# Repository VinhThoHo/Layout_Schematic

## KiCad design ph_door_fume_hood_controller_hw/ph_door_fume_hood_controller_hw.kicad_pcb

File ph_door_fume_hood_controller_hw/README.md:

# ph_door_fume_hood_controller_hw
This is hardware sample and reactor controller for project the door fume hood.

# Description

## Features:
    * Power input 24VDC (isolation 24VDC - 5VDC 1W)
    * 3 sensor input are activated at level low.
    * 4 output are activated at level low.
    * 4 input are activated at level high.
    * Control step mottor with current upto 4A.
    * Communication 485 (status, control signal,...), I2C, analog signal.
# Hardware
## Schematics

[Download](./ph_door_fume_hood_controller_hw.pdf)

## PCB Layout

## 3D Review

## Pinout

# Gerber

[Download](./gerber/gerber_ph_door_fume_hood_controller_hw.zip)

# BOMLIST

[Download](./assets/ph_door_fume_hood_controller_hw.csv)

# License

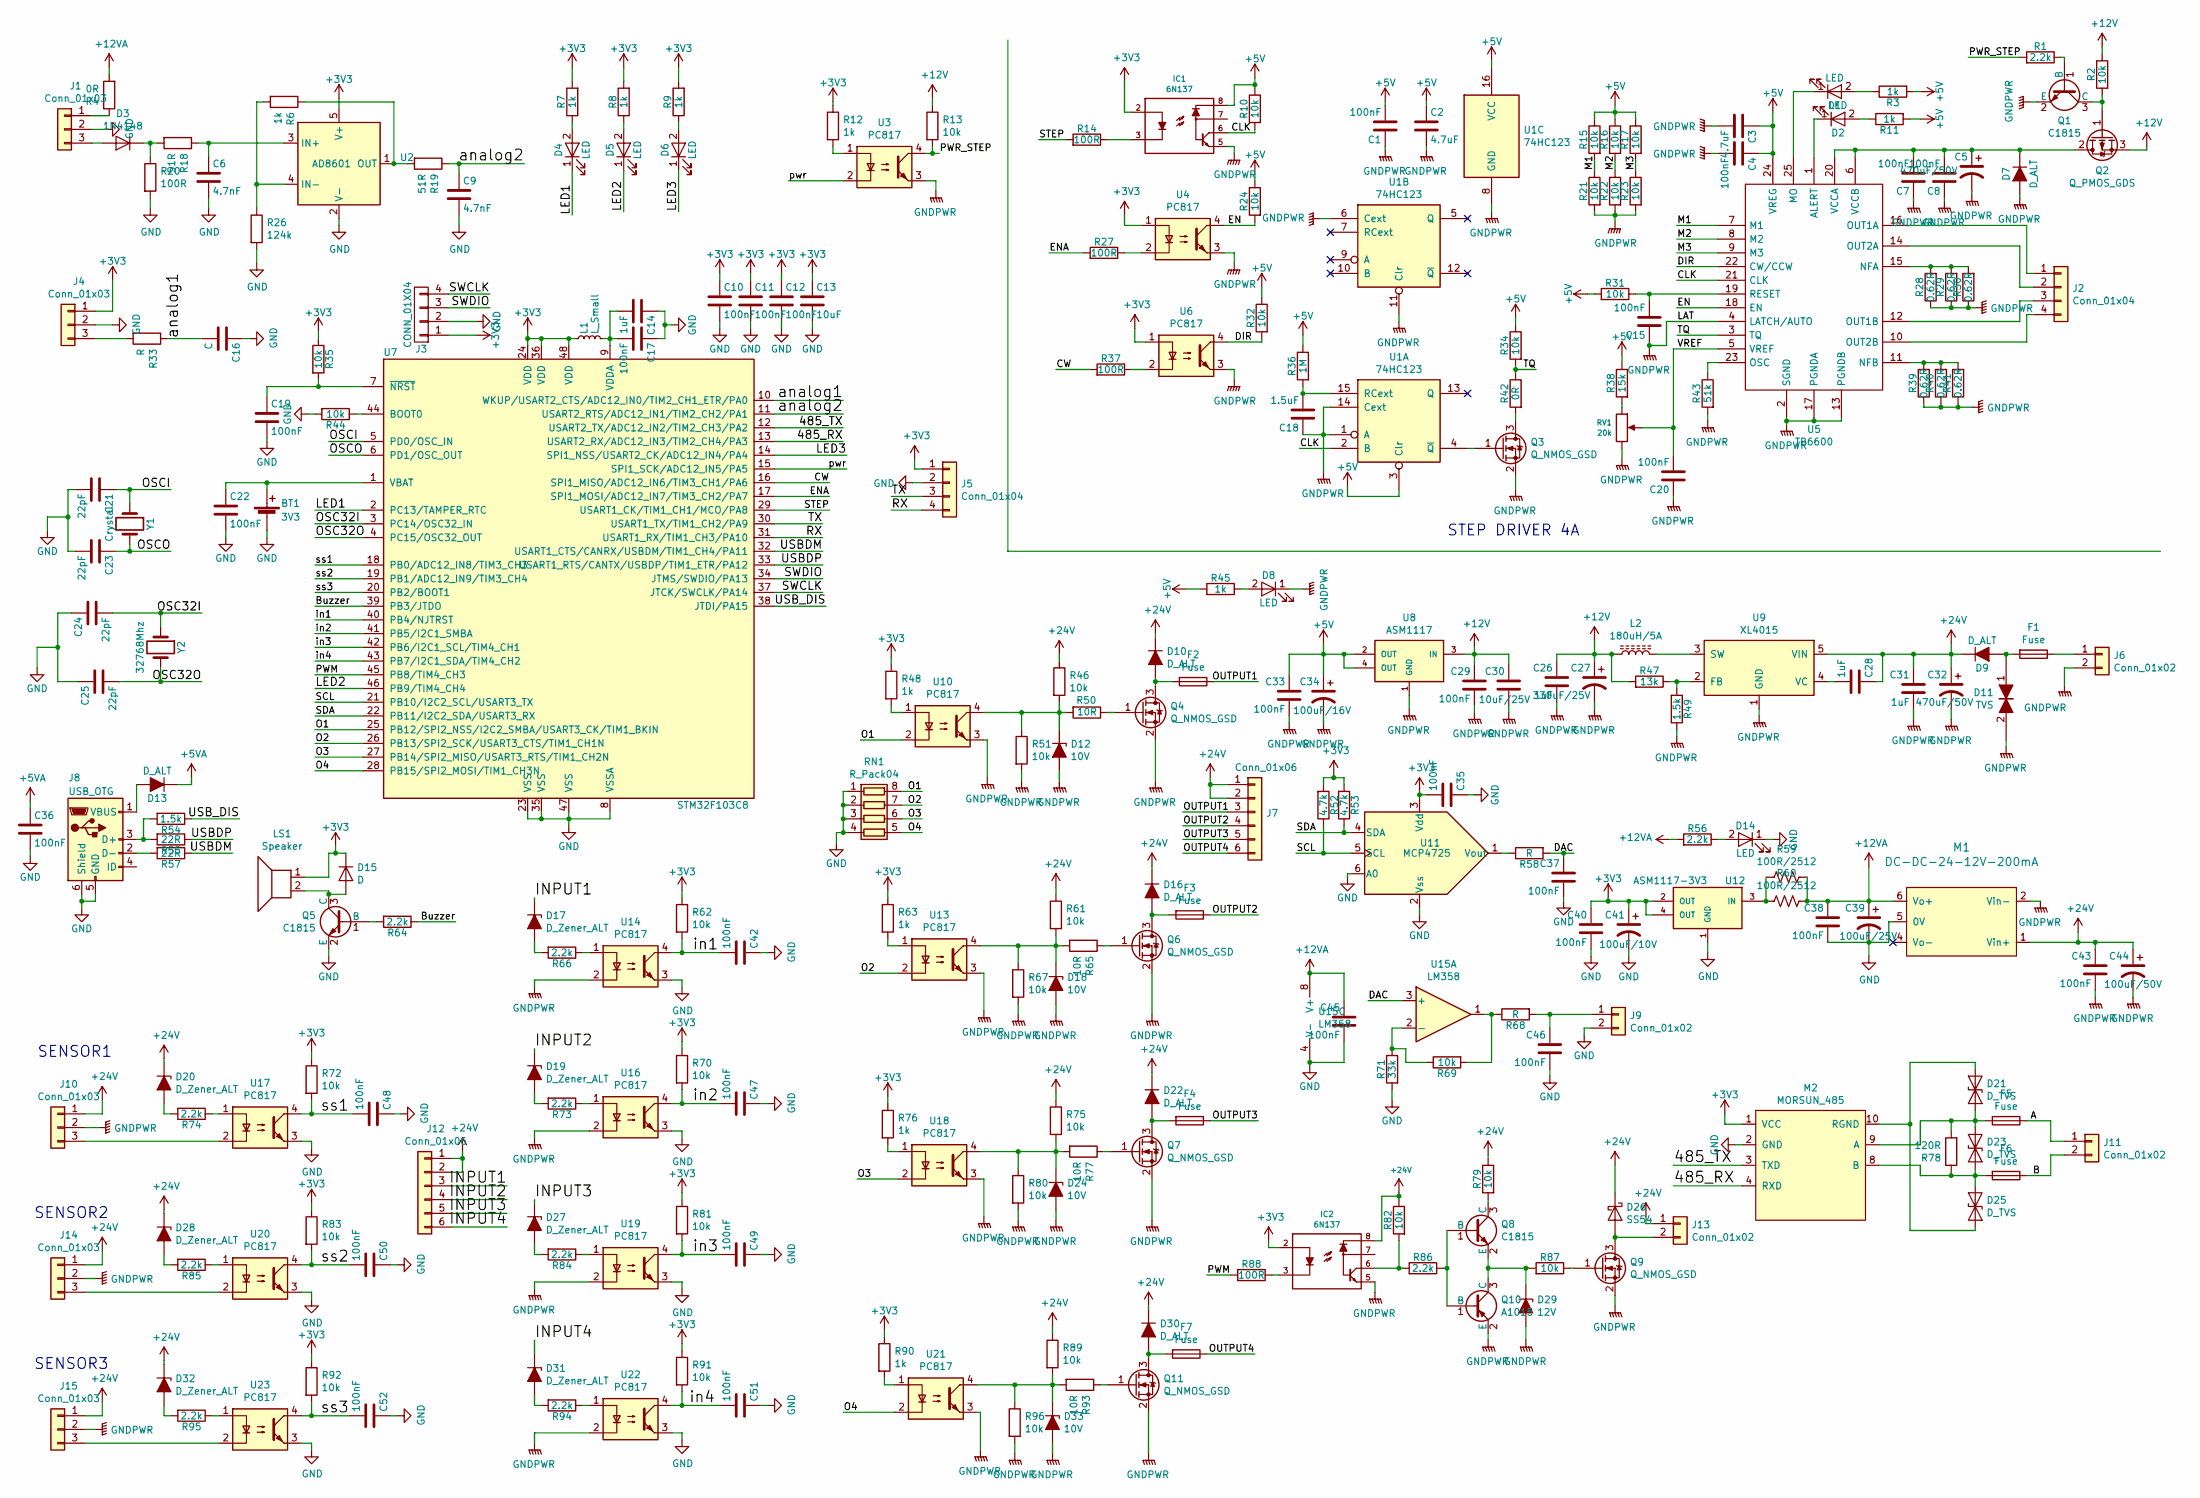
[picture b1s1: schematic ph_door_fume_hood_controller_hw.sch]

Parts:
BT1: 3V3; BT3V3
C1, C4, C7, C8, C10, C11, C12, C15, C17, C19, C20, C22, C29, C33, C35, C36, C37, C38, C40, C42, C43, C45, C46, C47, C48, C49, C50, C51, C52: 100nF; C_0805_2012Metric_Pad1.15x1.40mm_HandSolder
C2, C3: 4.7uF; C_1206_3216Metric_Pad1.42x1.75mm_HandSolder
C5: 470uF/50V; C_1210_3225Metric_Pad1.42x2.65mm_HandSolder
C6, C9: 4.7nF; C_0805_2012Metric_Pad1.15x1.40mm_HandSolder
C13: 10uF; C_1206_3216Metric_Pad1.42x1.75mm_HandSolder
C14, C26, C28, C31: 1uF; C_0805_2012Metric_Pad1.15x1.40mm_HandSolder
C16: C; C_0805_2012Metric_Pad1.15x1.40mm_HandSolder
C18: 1.5uF; C_0805_2012Metric_Pad1.15x1.40mm_HandSolder
C21, C23, C24, C25: 22pF; C_0805_2012Metric_Pad1.15x1.40mm_HandSolder
C27: 330uF/25V; CP_Elec_8x10.5
C30: 10uF/25V; C_1210_3225Metric_Pad1.42x2.65mm_HandSolder
C32: 470uF/50V; CP_Elec_10x14.3
C34: 100uF/16V; CP_Elec_6.3x5.4
C39: 100uF/25V; CP_EIA-7343-20_Kemet-V_Pad2.25x2.55mm_HandSolder
C41: 100uF/10V; CP_EIA-3528-15_AVX-H_Pad1.50x2.35mm_HandSolder
C44: 100uF/50V; CP_EIA-7343-31_Kemet-D_Pad2.25x2.55mm_HandSolder
D1, D2, D4, D5, D6, D8, D14: LED; LED_0805_2012Metric_Pad1.15x1.40mm_HandSolder
D3: 1N4148; D_SOD-323_HandSoldering
D7, D9, D10, D16, D22, D30: D_ALT; D_SMA_Standard
D11: TVS; D_SMA_Standard
D12, D18, D24, D33: 10V; SOD-80
D13: D_ALT; D_SOD-323F
D15: D; D_SOD-323F
D17, D19, D20, D27, D28, D31, D32: D_Zener_ALT; SOD-80
D21, D23, D25: D_TVS; D_SMA_Standard
D26: SS54; D_SMA_Standard
D29: 12V; SOD-80
F1: Fuse; Fuseholder5x20_horiz_SemiClosed_Casing10x25mm
F2, F3, F4, F5, F6, F7: Fuse; Fuse_SMD1812
IC1: 6N137; Diodes_PSOP-8
IC2: 6N137; SMDIP-8_W9.53mm
J1, J4: Conn_01x03; PinSocket_1x03_P2.54mm_Vertical
J2: Conn_01x04; TerminalBlock_WAGO-236_2Stift_R5mm_4pol
J3: CONN_01X04; PinHeader_1x04_P2.54mm_Vertical
J5: Conn_01x04; PinHeader_1x04_P2.54mm_Vertical
J6: Conn_01x02; TerminalBlock_WAGO-236_2Stift_R5mm_2pol
J7, J12: Conn_01x06; TerminalBlock_WAGO_2.54mm_6P
J8: USB_OTG; USB_Micro-B
J9: Conn_01x02; PinSocket_1x02_P2.54mm_Vertical
J10, J14, J15: Conn_01x03; TerminalBlock_WAGO_2.54mm_3P
J11, J13: Conn_01x02; TerminalBlock_WAGO_2.54mm_2P
L1: L_Small; L_0805_2012Metric_Pad1.15x1.40mm_HandSolder
L2: 180uH/5A; Inductor_5A
LS1: Speaker; Buzzer_15x7.5RM7.6
M1: DC-DC-24-12V-200mA; MORNSUN-A2412S-2W
M2: MORSUN_485
Q1, Q5, Q8: C1815; SOT-23
Q2: Q_PMOS_GDS; TO-252-2
Q3, Q4, Q6, Q7, Q9, Q11: Q_NMOS_GSD; SOT-23
Q10: A1015; SOT-23
R1, R56, R64, R66, R73, R74, R84, R85, R86, R94, R95: 2.2k; R_0805_2012Metric_Pad1.15x1.40mm_HandSolder
R2, R10, R13, R15, R16, R17, R21, R22, R23, R24, R31, R32, R34, R35, R44, R46, R51, R61, R62, R67, R69, R70, R72, R75, R79, R80, R81, R82, R83, R87, R89, R91, R92, R96: 10k; R_0805_2012Metric_Pad1.15x1.40mm_HandSolder
R3, R6, R7, R8, R9, R11, R12, R45, R48, R63, R76, R90: 1k; R_0805_2012Metric_Pad1.15x1.40mm_HandSolder
R4, R42: 0R; R_0805_2012Metric_Pad1.15x1.40mm_HandSolder
R14, R20, R27, R37, R88: 100R; R_0805_2012Metric_Pad1.15x1.40mm_HandSolder
R18, R19: 51R; R_0805_2012Metric_Pad1.15x1.40mm_HandSolder
R26: 124k; R_0805_2012Metric_Pad1.15x1.40mm_HandSolder
R28, R29, R30, R39, R40, R41: 0.62R; R_2512_6332Metric_Pad1.52x3.35mm_HandSolder
R33, R58, R68: R; R_0805_2012Metric_Pad1.15x1.40mm_HandSolder
R36: 1M; R_0805_2012Metric_Pad1.15x1.40mm_HandSolder
R38: 15k; R_0805_2012Metric_Pad1.15x1.40mm_HandSolder
R43: 51k; R_0805_2012Metric_Pad1.15x1.40mm_HandSolder
R47: 13k; R_0805_2012Metric_Pad1.15x1.40mm_HandSolder
R49, R54: 1.5k; R_0805_2012Metric_Pad1.15x1.40mm_HandSolder
R50, R65, R77, R93: 10R; R_0805_2012Metric_Pad1.15x1.40mm_HandSolder
R52, R53: 4.7k; R_0805_2012Metric_Pad1.15x1.40mm_HandSolder
R55, R57: 22R; R_0805_2012Metric_Pad1.15x1.40mm_HandSolder
R59, R60: 100R/2512; R_2512_6332Metric_Pad1.52x3.35mm_HandSolder
R71: 33k; R_0805_2012Metric_Pad1.15x1.40mm_HandSolder
R78: 120R; R_0805_2012Metric_Pad1.15x1.40mm_HandSolder
RN1: R_Pack04; R_Array_Convex_4x0603
RV1: 20k; VR-3362P
U1: 74HC123; SOIC-16W_5.3x10.2mm_Pitch1.27mm
U2: AD8601; SOT-23-5
U3, U4, U6, U10, U13, U14, U16, U17, U18, U19, U20, U21, U22, U23: PC817; Optocoupler_SMD
U5: TB6600
U7: STM32F103C8; LQFP-48_7x7mm_Pitch0.5mm
U8: ASM1117; SOT-223
U9: XL4015; TO-263-5_TabPin3
U11: MCP4725; SOT-23-6_Handsoldering
U12: ASM1117-3V3; SOT-223
U15: LM358; SOP-8_3.76x4.96mm_P1.27mm
Y1: Crystal; Crystal_SMD_HC49-SD
Y2: 32768Mhz; Crystal_Round_Horizontal_3mm_smd

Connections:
+3V3: C10.1, C11.1, C12.1, C13.1, C35.2, C40.1, C41.1, D15.1 (K), IC1.2, IC2.2, J3.1, J4.1, J5.1, L1.1, LS1.1, M2.1 (VCC), R7.2, R8.2, R9.2, R12.1, R35.1, R48.1, R52.2, R53.2, R62.1, R63.1, R70.1, R72.1, R76.1, R81.1, R83.1, R90.1, R91.1, R92.1, U2.5 (V+), U4.1, U6.1, U7.24 (VDD), U7.36 (VDD), U7.48 (VDD), U11.3 (Vdd), U12.2 (OUT), U12.4 (OUT)
+5V: C1.2, C2.1, C3.1, C4.1, C33.1, C34.1, IC1.8, R3.2, R10.1, R11.2, R15.1, R16.1, R17.1, R24.1, R31.2, R32.1, R34.1, R36.1, R38.1, R45.2, U1.3 (Clr), U1.16 (VCC), U5.24 (VREG), U8.2 (OUT), U8.4 (OUT)
+5VA: C36.1, D13.1 (K)
+12V: C26.1, C27.1, C29.1, C30.1, L2.1, Q2.3 (S), R2.1, R13.1, R47.2, U8.3 (IN)
+12VA: C38.1, C39.1, C45.1, M1.6 (Vo+), R4.2, R56.2, R59.1, R60.1, U15.8 (V+)
/485_RX: M2.4 (RXD), U7.13 (USART2_RX/ADC12_IN3/TIM2_CH4/PA3)
/485_TX: M2.3 (TXD), U7.12 (USART2_TX/ADC12_IN2/TIM2_CH3/PA2)
/A: F5.1, J11.1
/B: F6.1, J11.2
/Buzzer: R64.1, U7.39 (PB3/JTDO)
/CLK: IC1.6, R10.2, U1.2 (B), U5.21 (CLK)
/CW: R37.2, U7.16 (SPI1_MISO/ADC12_IN6/TIM3_CH1/PA6)
/DAC: C37.1, R58.2, U15.3 (+)
/DIR: R32.2, U5.22 (CW/CCW), U6.4
/EN: R24.2, U4.4, U5.18 (EN)
/ENA: R27.2, U7.17 (SPI1_MOSI/ADC12_IN7/TIM3_CH2/PA7)
/INPUT1: D17.1 (K), J12.3
/INPUT2: D19.1 (K), J12.4
/INPUT3: D27.1 (K), J12.5
/INPUT4: D31.1 (K), J12.6
/LED1: D4.1 (K), U7.2 (PC13/TAMPER_RTC)
/LED2: D5.1 (K), U7.46 (PB9/TIM4_CH4)
/LED3: D6.1 (K), U7.14 (SPI1_NSS/USART2_CK/ADC12_IN4/PA4)
/M1: R15.2, R21.1, U5.7 (M1)
/M2: R16.2, R22.1, U5.8 (M2)
/M3: R17.2, R23.1, U5.9 (M3)
/O1: RN1.8 (R1.2), U7.25 (PB12/SPI2_NSS/I2C2_SMBA/USART3_CK/TIM1_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), U10.2
/O2: RN1.7 (R2.2), U7.26 (PB13/SPI2_SCK/USART3_CTS/TIM1_CH1N), U13.2
/O3: RN1.6 (R3.2), U7.27 (PB14/SPI2_MISO/USART3_RTS/TIM1_CH2N), U18.2
/O4: RN1.5 (R4.2), U7.28 (PB15/SPI2_MOSI/TIM1_CH3N), U21.2
/OSC32I: C24.2, U7.3 (PC14/OSC32_IN), Y2.1
/OSC32O: C25.2, U7.4 (PC15/OSC32_OUT), Y2.2
/OSCI: C21.1, U7.5 (PD0/OSC_IN), Y1.1
/OSCO: C23.1, U7.6 (PD1/OSC_OUT), Y1.2
/OUTPUT1: F2.1, J7.3
/OUTPUT2: F3.1, J7.4
/OUTPUT3: F4.1, J7.5
/OUTPUT4: F7.1, J7.6
/PWM: R88.2, U7.45 (PB8/TIM4_CH3)
/PWR_STEP: R1.2, R13.2, U3.4
/RX: J5.4, U7.31 (USART1_RX/TIM1_CH3/PA10)
/SCL: R52.1, U7.21 (PB10/I2C2_SCL/USART3_TX), U11.5 (SCL)
/SDA: R53.1, U7.22 (PB11/I2C2_SDA/USART3_RX), U11.4 (SDA)
/STEP: R14.2, U7.29 (USART1_CK/TIM1_CH1/MCO/PA8)
/SWCLK: J3.4, U7.37 (JTCK/SWCLK/PA14)
/SWDIO: J3.3, U7.34 (JTMS/SWDIO/PA13)
/TQ: R34.2, R42.1, U5.3 (TQ)
/TX: J5.3, U7.30 (USART1_TX/TIM1_CH2/PA9)
/USBDM: R57.1, U7.32 (USART1_CTS/CANRX/USBDM/TIM1_CH4/PA11)
/USBDP: R55.1, U7.33 (USART1_RTS/CANTX/USBDP/TIM1_ETR/PA12)
/USB_DIS: R54.1, U7.38 (JTDI/PA15)
/VREF: C20.2, RV1.2, U5.5 (VREF)
/analog1: C16.2, R33.1, U7.10 (WKUP/USART2_CTS/ADC12_IN0/TIM2_CH1_ETR/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)
/analog2: C9.1, R19.1, U7.11 (USART2_RTS/ADC12_IN1/TIM2_CH2/PA1)
/in1: C42.2, R62.2, U7.40 (PB4/NJTRST), U14.4
/in2: C47.2, R70.2, U7.41 (PB5/I2C1_SMBA), U16.4
/in3: C49.2, R81.2, U7.42 (PB6/I2C1_SCL/TIM4_CH1), U19.4
/in4: C51.2, R91.2, U7.43 (PB7/I2C1_SDA/TIM4_CH2), U22.4
/pwr: U3.2, U7.15 (SPI1_SCK/ADC12_IN5/PA5)
/ss1: C48.2, R72.2, U7.18 (PB0/ADC12_IN8/TIM3_CH3), U17.4
/ss2: C50.2, R83.2, U7.19 (PB1/ADC12_IN9/TIM3_CH4), U20.4
/ss3: C52.2, R92.2, U7.20 (PB2/BOOT1), U23.4
GND: BT1.2 (-), C6.2, C9.2, C10.2, C11.2, C12.2, C13.2, C14.1, C16.1, C17.1, C19.2, C21.2, C22.2, C23.2, C24.1, C25.1, C35.1, C36.2, C37.2, C38.2, C39.2, C40.2, C41.2, C42.1, C45.2, C46.2, C47.1, C48.1, C49.1, C50.1, C51.1, C52.1, D14.1 (K), J1.2, J3.2, J4.2, J5.2, J8.5 (GND), J8.6 (Shield), J9.2, M1.5 (0V), M2.2 (GND), Q5.2 (E), R20.2, R26.2, R44.2, R71.2, RN1.1 (R1.1), RN1.2 (R2.1), RN1.3 (R3.1), RN1.4 (R4.1), U2.2 (V-), U7.8 (VSSA), U7.23 (VSS), U7.35 (VSS), U7.47 (VSS), U11.2 (Vss), U11.6 (A0), U12.1 (GND), U14.3, U15.4 (V-), U16.3, U17.3, U19.3, U20.3, U22.3, U23.3
GNDPWR: C1.1, C2.2, C3.2, C4.2, C5.2, C7.1, C8.1, C15.1, C18.1, C20.1, C26.2, C27.2, C29.2, C30.2, C31.2, C32.2, C33.2, C34.2, C43.2, C44.2, D7.2 (A), D8.1 (K), D11.2, D12.2 (A), D18.2 (A), D24.2 (A), D29.2 (A), D33.2 (A), IC1.5, IC2.5, J6.2, J10.2, J14.2, J15.2, M1.2 (Vin-), Q1.2 (E), Q3.2 (S), Q4.2 (S), Q6.2 (S), Q7.2 (S), Q9.2 (S), Q10.2 (E), Q11.2 (S), R21.2, R22.2, R23.2, R28.1, R29.1, R30.1, R39.1, R40.1, R41.1, R43.2, R49.1, R51.2, R67.2, R80.2, R96.2, RV1.3, U1.1 (A), U1.6 (Cext), U1.8 (GND), U1.11 (Clr), U1.14 (Cext), U3.3, U4.3, U5.2 (SGND), U5.4 (LATCH/AUTO), U5.13 (PGNDB), U5.17 (PGNDA), U6.3, U8.1 (GND), U9.1 (GND), U10.3, U13.3, U14.2, U16.2, U18.3, U19.2, U21.3, U22.2
unnamed: BT1.1 (+), C22.1, U7.1 (VBAT)
unnamed: C5.1, C7.2, C8.2, D7.1 (K), Q2.2 (D), U5.6 (VCCB), U5.20 (VCCA)
unnamed: C6.1, R18.1, U2.3 (IN+)
unnamed: C14.2, C17.2, L1.2, U7.9 (VDDA)
unnamed: C15.2, R31.1, U5.19 (RESET)
unnamed: C18.2, R36.2, U1.15 (RCext)
unnamed: C19.1, R35.2, U7.7 (~NRST)
unnamed: C28.2, U9.4 (VC)
unnamed: C46.1, J9.1, R68.2
unnamed: D1.1 (K), U5.25 (MO)
unnamed: D1.2 (A), R3.1
unnamed: D2.1 (K), U5.1 (ALERT)
unnamed: D2.2 (A), R11.1
unnamed: D3.1 (K), R18.2, R20.1
unnamed: D3.2 (A), J1.3
unnamed: D4.2 (A), R7.1
unnamed: D5.2 (A), R8.1
unnamed: D6.2 (A), R9.1
unnamed: D8.2 (A), R45.1
unnamed: D10.2 (A), F2.2, Q4.3 (D)
unnamed: D9.2 (A), D11.1, F1.2
unnamed: D12.1 (K), R46.2, R50.2, R51.1, U10.4
unnamed: D13.2 (A), J8.1 (VBUS)
unnamed: D14.2 (A), R56.1
unnamed: D15.2 (A), LS1.2, Q5.3 (C)
unnamed: D16.2 (A), F3.2, Q6.3 (D)
unnamed: D17.2 (A), R66.2
unnamed: D18.1 (K), R61.2, R65.2, R67.1, U13.4
unnamed: D19.2 (A), R73.2
unnamed: D20.2 (A), R74.2
unnamed: D21.1 (A1), D25.2 (A2), M2.10 (RGND)
unnamed: D21.2 (A2), D23.1 (A1), F5.2, M2.9 (A), R78.2
unnamed: D22.2 (A), F4.2, Q7.3 (D)
unnamed: D23.2 (A2), D25.1 (A1), F6.2, M2.8 (B), R78.1
unnamed: D24.1 (K), R75.2, R77.2, R80.1, U18.4
unnamed: D26.2 (A), J13.2, Q9.3 (D)
unnamed: D27.2 (A), R84.2
unnamed: D28.2 (A), R85.2
unnamed: D29.1 (K), Q8.2 (E), Q10.3 (C), R87.2
unnamed: D30.2 (A), F7.2, Q11.3 (D)
unnamed: D31.2 (A), R94.2
unnamed: D32.2 (A), R95.2
unnamed: D33.1 (K), R89.2, R93.2, R96.1, U21.4
unnamed: F1.1, J6.1
unnamed: IC1.3, R14.1
unnamed: IC2.3, R88.1
unnamed: IC2.6, R82.2, R86.2
unnamed: J1.1, R4.1
unnamed: J2.1, U5.16 (OUT1A)
unnamed: J2.2, U5.14 (OUT2A)
unnamed: J2.3, U5.12 (OUT1B)
unnamed: J2.4, U5.10 (OUT2B)
unnamed: J4.3, R33.2
unnamed: J8.2 (D-), R57.2
unnamed: J8.3 (D+), R54.2, R55.2
unnamed: J10.3, U17.2
unnamed: J14.3, U20.2
unnamed: J15.3, U23.2
unnamed: L2.2, U9.3 (SW)
unnamed: Q1.1 (B), R1.1
unnamed: Q1.3 (C), Q2.1 (G), R2.2
unnamed: Q3.1 (G), U1.4 (~Q)
unnamed: Q3.3 (D), R42.2
unnamed: Q4.1 (G), R50.1
unnamed: Q5.1 (B), R64.2
unnamed: Q6.1 (G), R65.1
unnamed: Q7.1 (G), R77.1
unnamed: Q8.3 (C), R79.2
unnamed: Q9.1 (G), R87.1
unnamed: Q8.1 (B), Q10.1 (B), R86.1
unnamed: Q11.1 (G), R93.1
unnamed: R12.2, U3.1
unnamed: R6.1, R19.2, U2.1 (OUT)
unnamed: R6.2, R26.1, U2.4 (IN-)
unnamed: R27.1, U4.2
unnamed: R28.2, R29.2, R30.2, U5.15 (NFA)
unnamed: R37.1, U6.2
unnamed: R38.2, RV1.1
unnamed: R39.2, R40.2, R41.2, U5.11 (NFB)
unnamed: R43.1, U5.23 (OSC)
unnamed: R44.1, U7.44 (BOOT0)
unnamed: R47.1, R49.2, U9.2 (FB)
unnamed: R48.2, U10.1
unnamed: R58.1, U11.1 (Vout)
unnamed: R59.2, R60.2, U12.3 (IN)
unnamed: R63.2, U13.1
unnamed: R66.1, U14.1
unnamed: R68.1, R69.2, U15.1
unnamed: R69.1, R71.1, U15.2 (-)
unnamed: R73.1, U16.1
unnamed: R74.1, U17.1
unnamed: R76.2, U18.1
unnamed: R84.1, U19.1
unnamed: R85.1, U20.1
unnamed: R90.2, U21.1
unnamed: R94.1, U22.1
unnamed: R95.1, U23.1

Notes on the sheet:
STEP DRIVER 4A
SENSOR1
SENSOR2
SENSOR3

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
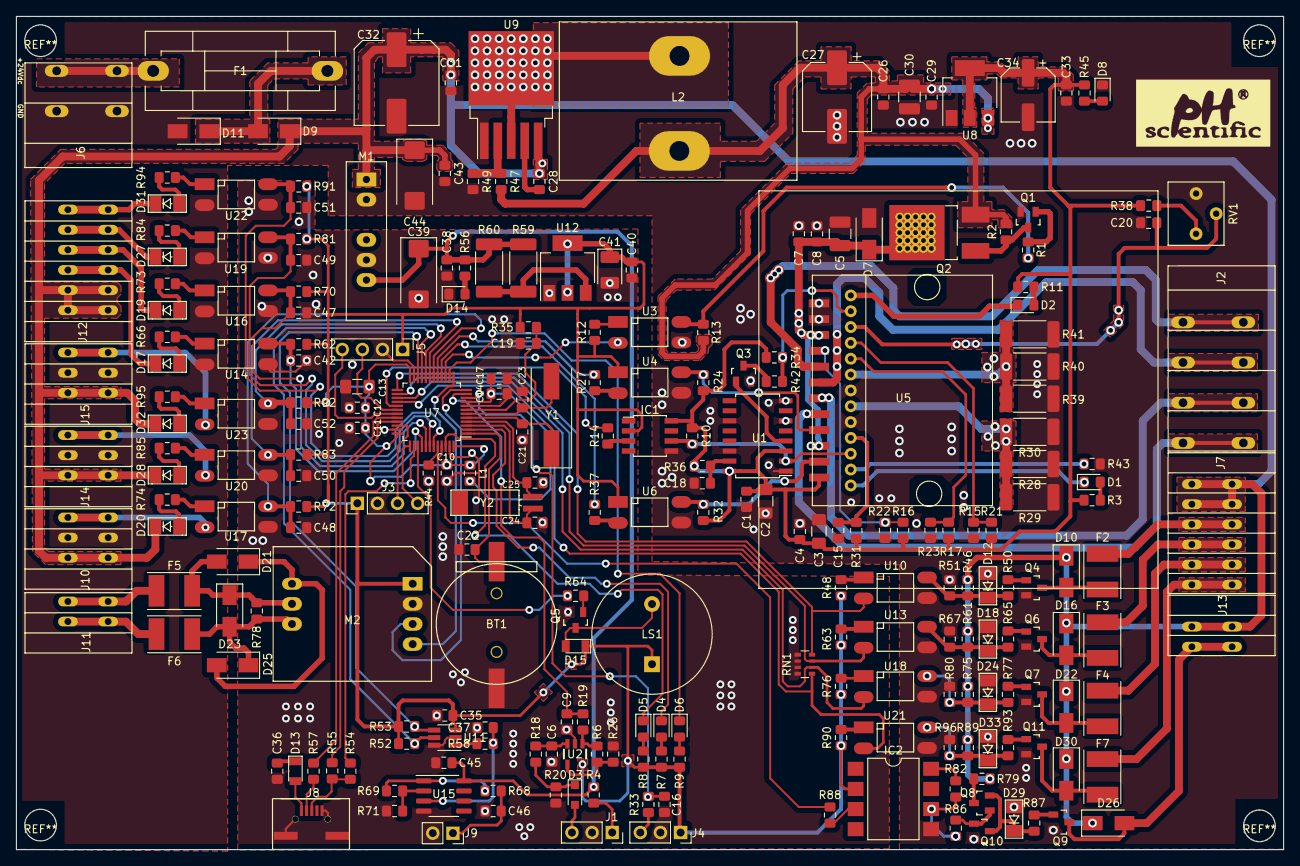
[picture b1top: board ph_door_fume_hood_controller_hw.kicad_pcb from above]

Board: 2 copper layers, 160.0 x 105.2 mm, 247 parts (0 on the bottom side), 163 nets.

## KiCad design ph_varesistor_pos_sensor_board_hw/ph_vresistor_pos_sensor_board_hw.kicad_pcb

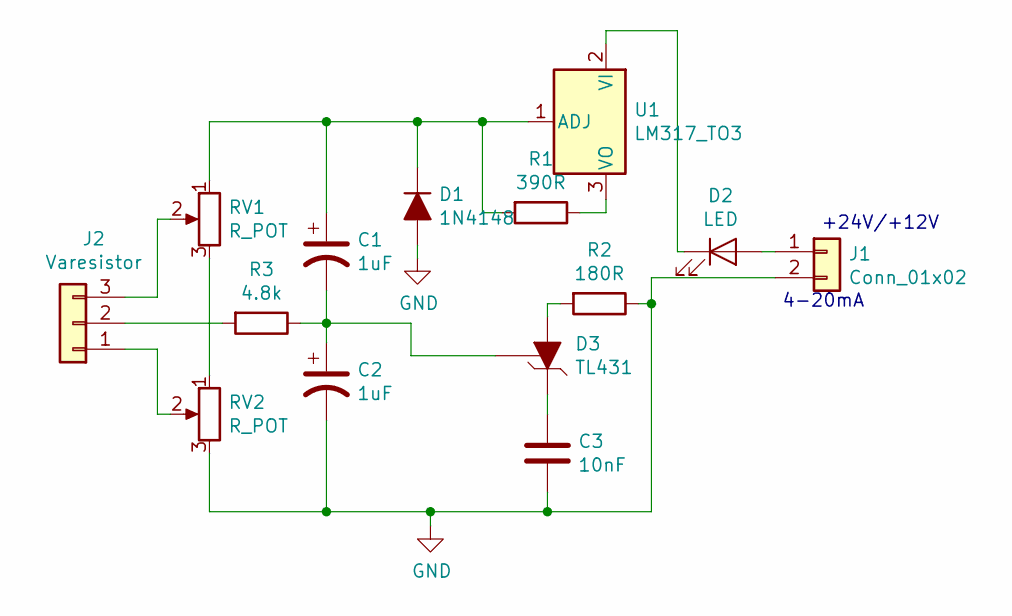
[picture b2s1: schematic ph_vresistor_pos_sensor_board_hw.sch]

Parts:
C1, C2: 1uF; C_0805_2012Metric_Pad1.15x1.40mm_HandSolder
C3: 10nF; C_0805_2012Metric_Pad1.15x1.40mm_HandSolder
D1: 1N4148; D_SOD-323_HandSoldering
D2: LED; LED_0805_2012Metric_Pad1.15x1.40mm_HandSolder
D3: TL431; SOT-23
J1: Conn_01x02; PinHeader_1x02_P2.54mm_Vertical
J2: Varesistor; Varesistor Bourns
R1: 390R; R_0805_2012Metric_Pad1.15x1.40mm_HandSolder
R2: 180R; R_0805_2012Metric_Pad1.15x1.40mm_HandSolder
R3: 4.8k; R_0805_2012Metric_Pad1.15x1.40mm_HandSolder
RV1, RV2: R_POT; VR1
U1: LM317_TO3; TO-252-2

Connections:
GND: C2.2, C3.2, D1.2 (A), J1.2, R2.1, RV2.3
unnamed: C1.1, D1.1 (K), R1.2, RV1.1, U1.1 (ADJ)
unnamed: C1.2, C2.1, D3.1 (R), R3.1
unnamed: C3.1, D3.3 (K)
unnamed: D2.1 (K), U1.2 (VI)
unnamed: D2.2 (A), J1.1
unnamed: D3.2 (A), R2.2
unnamed: J2.1, RV2.2
unnamed: J2.2, R3.2
unnamed: J2.3, RV1.2
unnamed: R1.1, U1.3 (VO)
unnamed: RV1.3, RV2.1

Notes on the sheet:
+24V/+12V
4-20mA

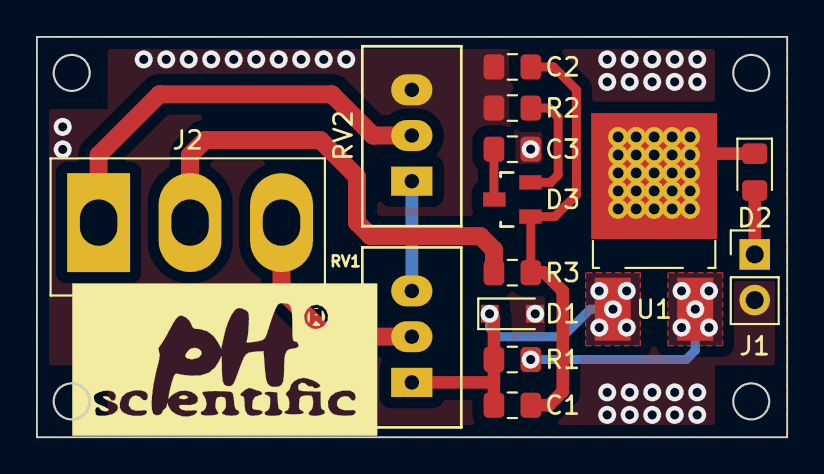
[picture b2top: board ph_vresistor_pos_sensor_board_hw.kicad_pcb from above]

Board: 2 copper layers, 41.7 x 22.2 mm, 14 parts (0 on the bottom side), 12 nets.

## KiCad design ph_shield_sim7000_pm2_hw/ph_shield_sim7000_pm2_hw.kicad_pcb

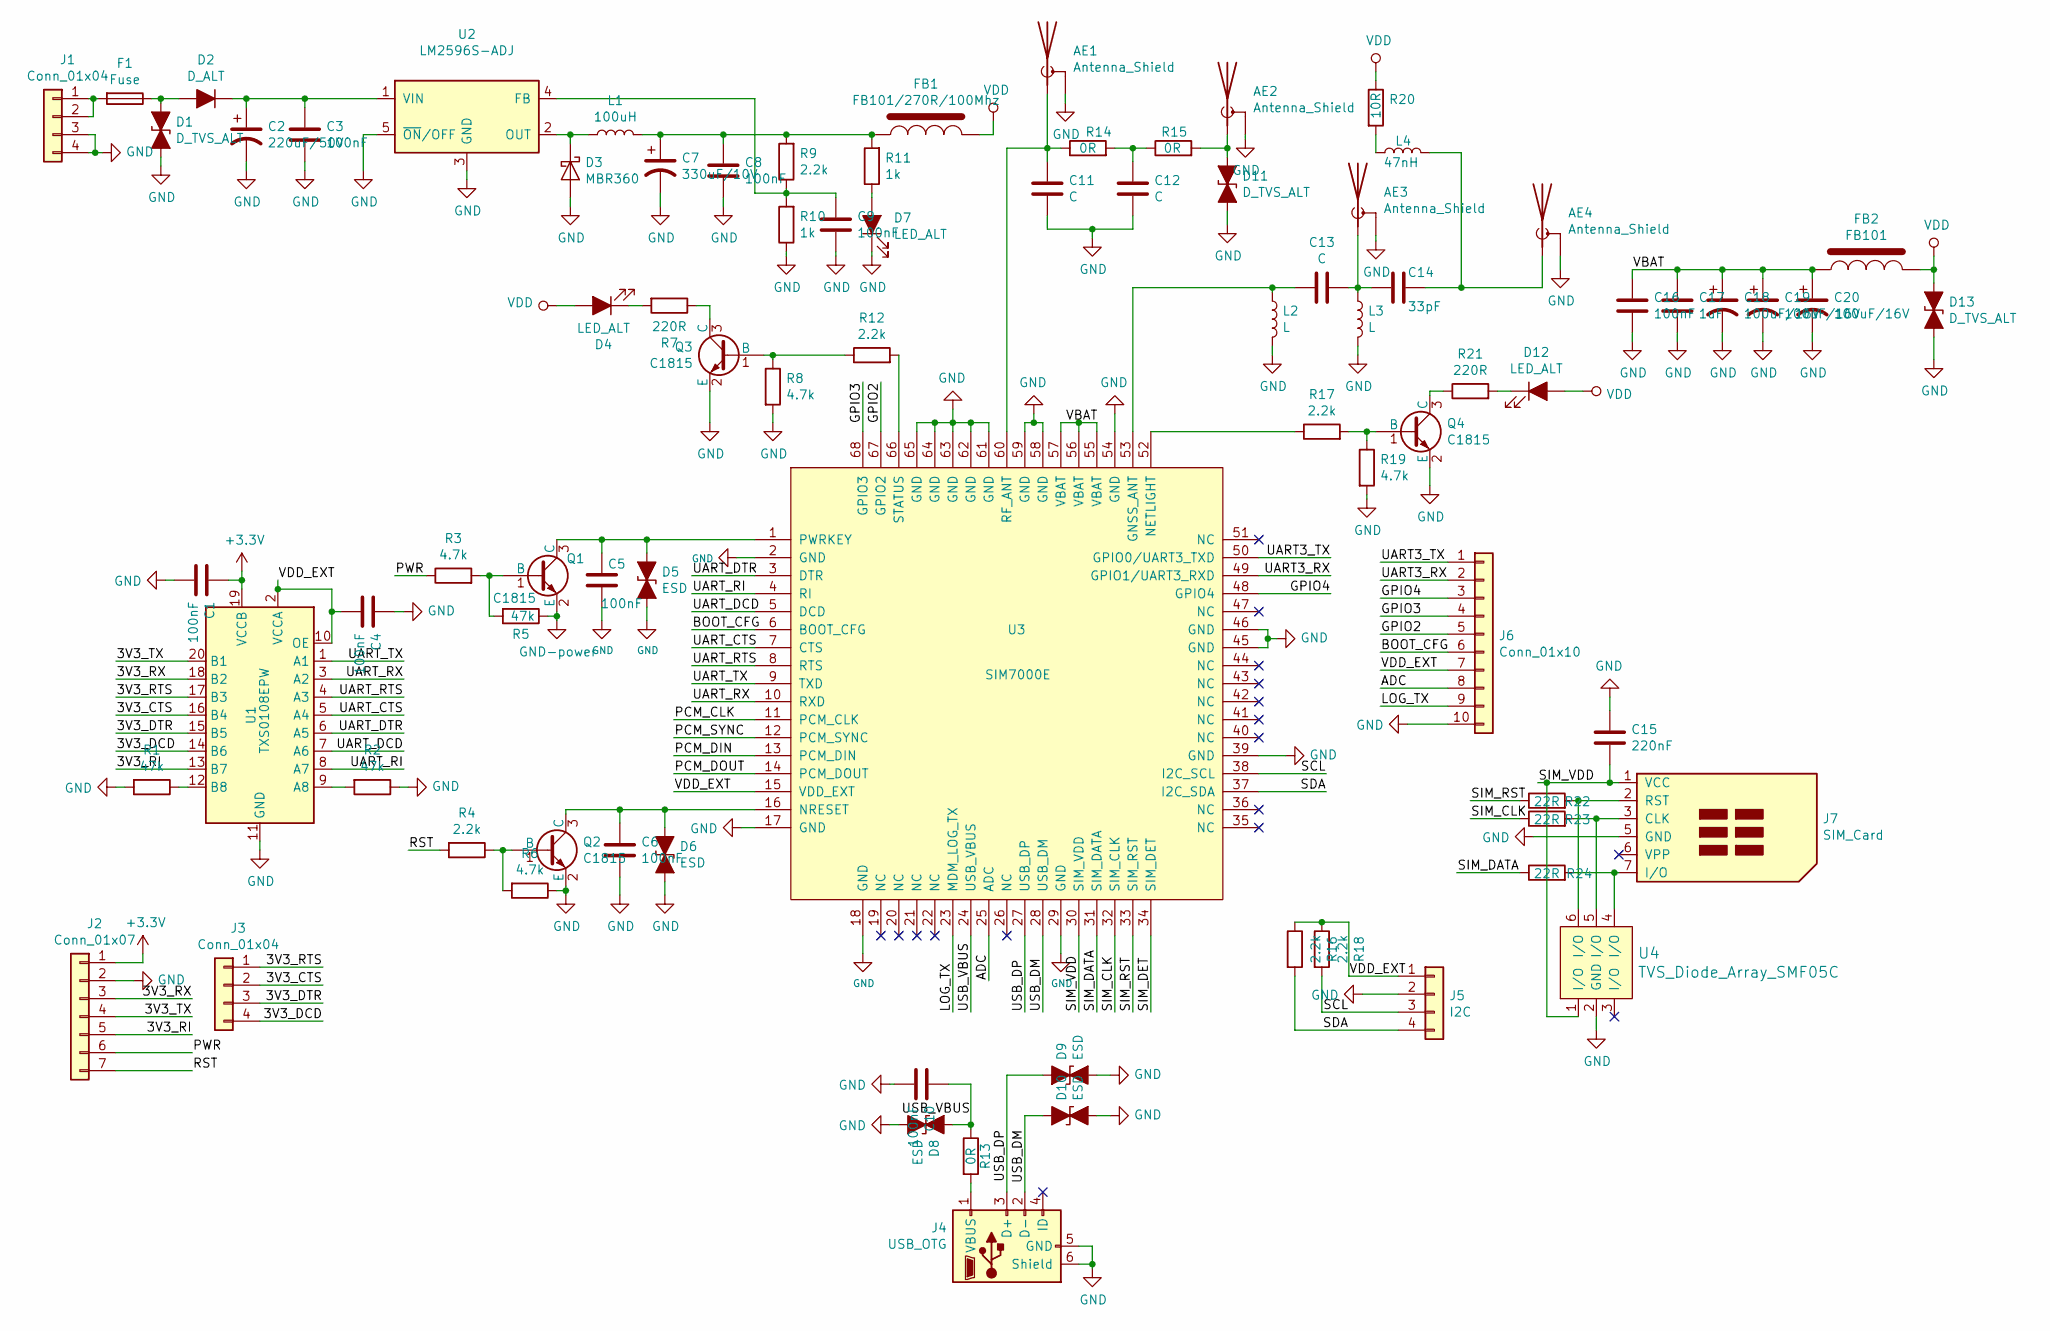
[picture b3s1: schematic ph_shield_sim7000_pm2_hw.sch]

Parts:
AE1, AE3: Antenna_Shield; Anten_GSM_IPEX
AE2, AE4: Antenna_Shield; Anten_GPS
C1, C3, C4, C5, C6, C8, C9, C10, C16: 100nF; C_0805_HandSoldering
C2: 220uF/50V; CP_Elec_10x10.5
C7: 330uF/10V; CP_EIA-7343-30_AVX-N_Pad2.25x2.55mm_HandSolder
C11, C12, C13: C; C_0805_HandSoldering
C14: 33pF; C_0805_HandSoldering
C15: 220nF; C_0805_HandSoldering
C17: 1uF; C_0805_HandSoldering
C18, C19, C20: 100uF/16V; CP_EIA-6032-28_Kemet-C_Pad2.25x2.35mm_HandSolder
D1, D11, D13: D_TVS_ALT; D_SMA_Standard
D2: D_ALT; D_SMA_Standard
D3: MBR360; DO-214AA
D4, D7, D12: LED_ALT; LED_0805_HandSoldering
D5, D6, D8, D9, D10: ESD; D_SOD-323_HandSoldering
F1: Fuse; Fuse_SMD1812
FB1: FB101/270R/100Mhz; R_0805_2012Metric_Pad1.15x1.40mm_HandSolder
FB2: FB101; R_0805_2012Metric_Pad1.15x1.40mm_HandSolder
J1: Conn_01x04; Header-4pin-2.54
J2: Conn_01x07; PinHeader_1x07_P2.54mm_Vertical
J3: Conn_01x04; PinHeader_1x04_P2.54mm_Vertical
J4: USB_OTG; USB_Micro-B
J5: I2C; PinHeader_1x04_P2.54mm_Vertical
J6: Conn_01x10; PinHeader_1x10_P2.00mm_Vertical
J7: SIM_Card; socket_sim_6p
L1: 100uH; L_
L2, L3: L; R_0805_2012Metric_Pad1.15x1.40mm_HandSolder
L4: 47nH; C_0603_1608Metric_Pad1.05x0.95mm_HandSolder
Q1, Q2, Q3, Q4: C1815; SOT-23
R1, R2, R5: 47k; R_0603_1608Metric_Pad1.05x0.95mm_HandSolder
R3, R6, R8, R19: 4.7k; R_0603_1608Metric_Pad1.05x0.95mm_HandSolder
R4, R9, R12, R16, R17, R18: 2.2k; R_0603_1608Metric_Pad1.05x0.95mm_HandSolder
R7, R21: 220R; R_0603_1608Metric_Pad1.05x0.95mm_HandSolder
R10, R11: 1k; R_0603_1608Metric_Pad1.05x0.95mm_HandSolder
R13, R14, R15: 0R; R_0805_HandSoldering
R20: 10R; R_0603_1608Metric_Pad1.05x0.95mm_HandSolder
R22, R23, R24: 22R; R_0603_1608Metric_Pad1.05x0.95mm_HandSolder
U1: TXS0108EPW; TSSOP-20_4.4x6.5mm_P0.65mm
U2: LM2596S-ADJ; TO-263-5_TabPin3
U3: SIM7000E; SIM7000e
U4: TVS_Diode_Array_SMF05C; SOT-363_SC-70-6_Handsoldering

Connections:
+3V3: C1.1, J2.1, U1.19 (VCCB)
/3V3_CTS: J3.2, U1.16 (B4)
/3V3_DCD: J3.4, U1.14 (B6)
/3V3_DTR: J3.3, U1.15 (B5)
/3V3_RI: J2.5, U1.13 (B7)
/3V3_RTS: J3.1, U1.17 (B3)
/3V3_RX: J2.3, U1.18 (B2)
/3V3_TX: J2.4, U1.20 (B1)
/ADC: J6.8, U3.25 (ADC)
/BOOT_CFG: J6.6, U3.6 (BOOT_CFG)
/GPIO2: J6.5, U3.67 (GPIO2)
/GPIO3: J6.4, U3.68 (GPIO3)
/GPIO4: J6.3, U3.48 (GPIO4)
/LOG_TX: J6.9, U3.23 (MDM_LOG_TX)
/PCM_CLK: U3.11 (PCM_CLK)
/PCM_DIN: U3.13 (PCM_DIN)
/PCM_DOUT: U3.14 (PCM_DOUT)
/PCM_SYNC: U3.12 (PCM_SYNC)
/PWR: J2.6, R3.1
/RST: J2.7, R4.2
/SCL: J5.3, R18.2, U3.38 (I2C_SCL)
/SDA: J5.4, R16.2, U3.37 (I2C_SDA)
/SIM_CLK: R23.1, U3.32 (SIM_CLK)
/SIM_DATA: R24.1, U3.31 (SIM_DATA)
/SIM_DET: U3.34 (SIM_DET)
/SIM_RST: R22.1, U3.33 (SIM_RST)
/SIM_VDD: C15.1, J7.1 (VCC), U3.30 (SIM_VDD), U4.1 (I/O)
/UART3_RX: J6.2, U3.49 (GPIO1/UART3_RXD)
/UART3_TX: J6.1, U3.50 (GPIO0/UART3_TXD)
/UART_CTS: U1.5 (A4), U3.7 (CTS)
/UART_DCD: U1.7 (A6), U3.5 (DCD)
/UART_DTR: U1.6 (A5), U3.3 (DTR)
/UART_RI: U1.8 (A7), U3.4 (RI)
/UART_RTS: U1.4 (A3), U3.8 (RTS)
/UART_RX: U1.3 (A2), U3.10 (RXD)
/UART_TX: U1.1 (A1), U3.9 (TXD)
/USB_DM: D10.1 (A1), J4.2 (D-), U3.28 (USB_DM)
/USB_DP: D9.1 (A1), J4.3 (D+), U3.27 (USB_DP)
/USB_VBUS: C10.2, D8.1 (A1), R13.1, U3.24 (USB_VBUS)
/VBAT: C16.1, C17.1, C18.1, C19.1, C20.1, FB2.1, U3.55 (VBAT), U3.56 (VBAT), U3.57 (VBAT)
/VDD_EXT: C4.2, J5.1, J6.7, R16.1, R18.1, U1.2 (VCCA), U1.10 (OE), U3.15 (VDD_EXT)
unnamed: AE1.1 (A), C11.1, R14.1, U3.60 (RF_ANT)
unnamed: AE2.1 (A), D11.1 (A1), R15.2
unnamed: AE3.1 (A), C13.1, C14.2, L3.1
unnamed: AE4.1 (A), C14.1, L4.2
unnamed: C2.1, C3.1, D2.1 (K), U2.1 (VIN)
unnamed: C5.1, D5.1 (A1), Q1.3 (C), U3.1 (PWRKEY)
unnamed: C6.1, D6.1 (A1), Q2.3 (C), U3.16 (NRESET)
unnamed: C7.1, C8.1, FB1.1, L1.2, R9.2, R11.2
unnamed: C9.1, R9.1, R10.2, U2.4 (FB)
unnamed: C12.1, R14.2, R15.1
unnamed: C13.2, L2.1, U3.53 (GNSS_ANT)
unnamed: D1.1 (A1), D2.2 (A), F1.1
unnamed: D3.1 (K), L1.1, U2.2 (OUT)
unnamed: D4.1 (K), R7.2
unnamed: D7.2 (A), R11.1
unnamed: D12.1 (K), R21.2
unnamed: F1.2, J1.1, J1.2
unnamed: J4.1 (VBUS), R13.2
unnamed: J7.2 (RST), R22.2, U4.6 (I/O)
unnamed: J7.3 (CLK), R23.2, U4.5 (I/O)
unnamed: J7.7 (I/O), R24.2, U4.4 (I/O)
unnamed: L4.1, R20.2
unnamed: Q1.1 (B), R3.2, R5.2
unnamed: Q2.1 (B), R4.1, R6.2
unnamed: Q3.1 (B), R8.1, R12.1
unnamed: Q3.3 (C), R7.1
unnamed: Q4.1 (B), R17.2, R19.1
unnamed: Q4.3 (C), R21.1
unnamed: R1.1, U1.12 (B8)
unnamed: R2.2, U1.9 (A8)
unnamed: R12.2, U3.66 (STATUS)
unnamed: R17.1, U3.52 (NETLIGHT)
VDD: D4.2 (A), D12.2 (A), D13.1 (A1), FB1.2, FB2.2, R20.1

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
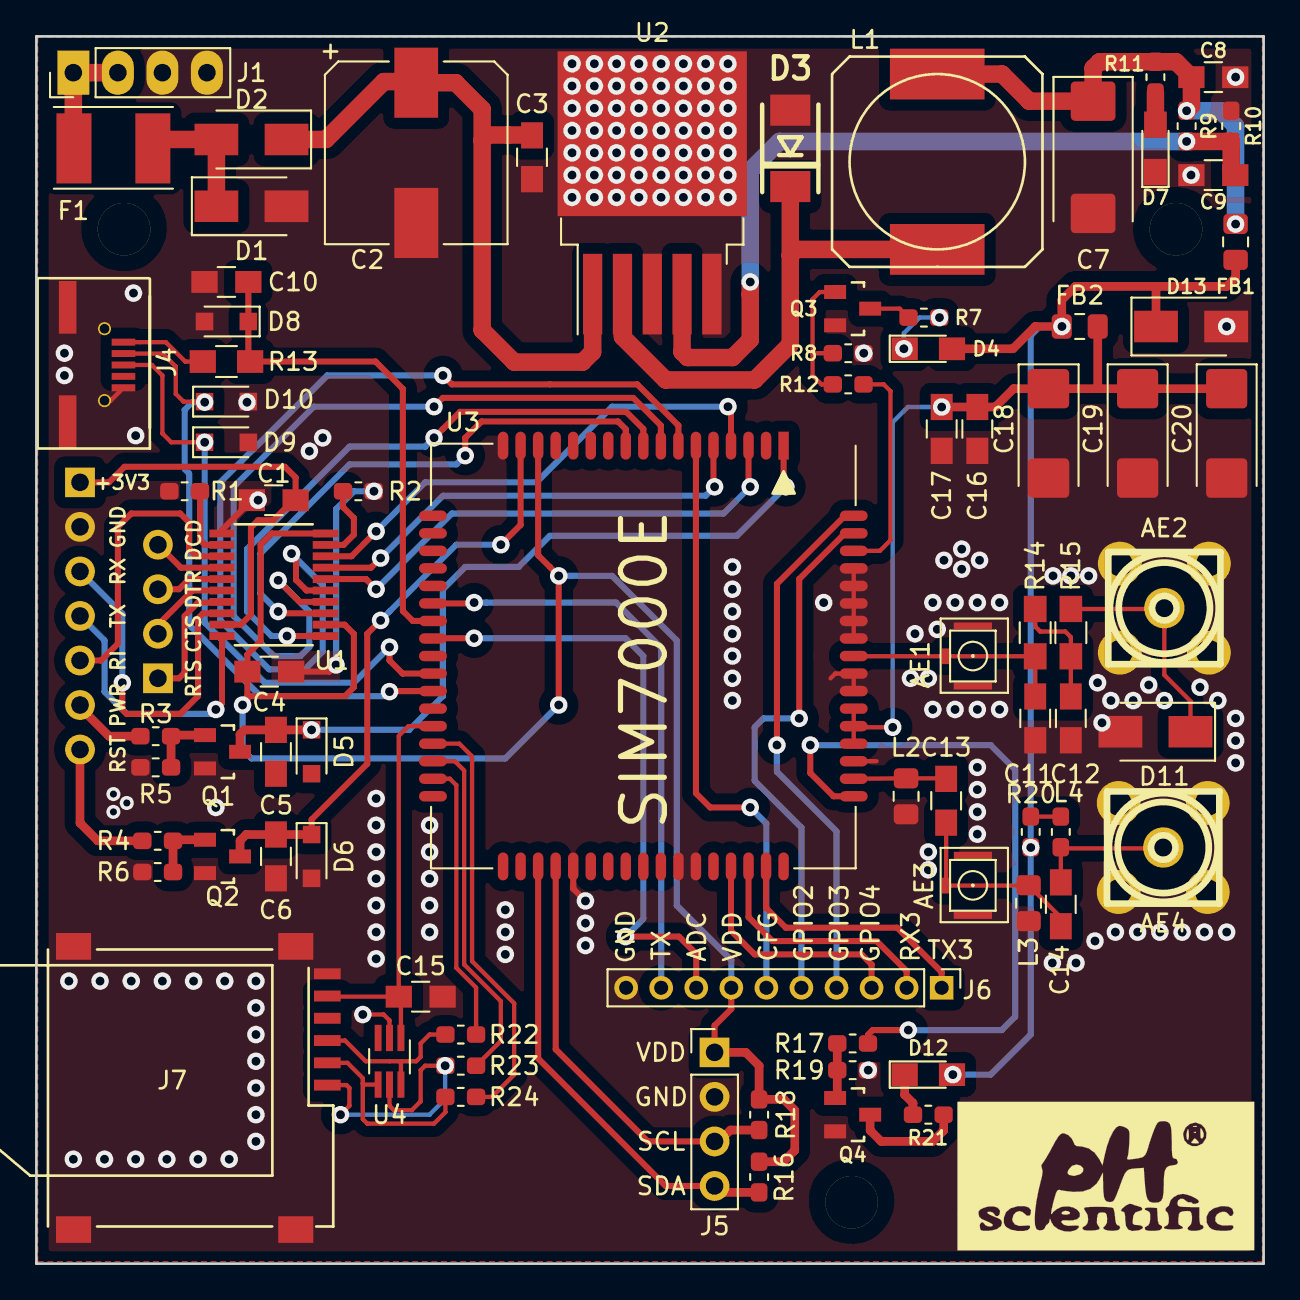
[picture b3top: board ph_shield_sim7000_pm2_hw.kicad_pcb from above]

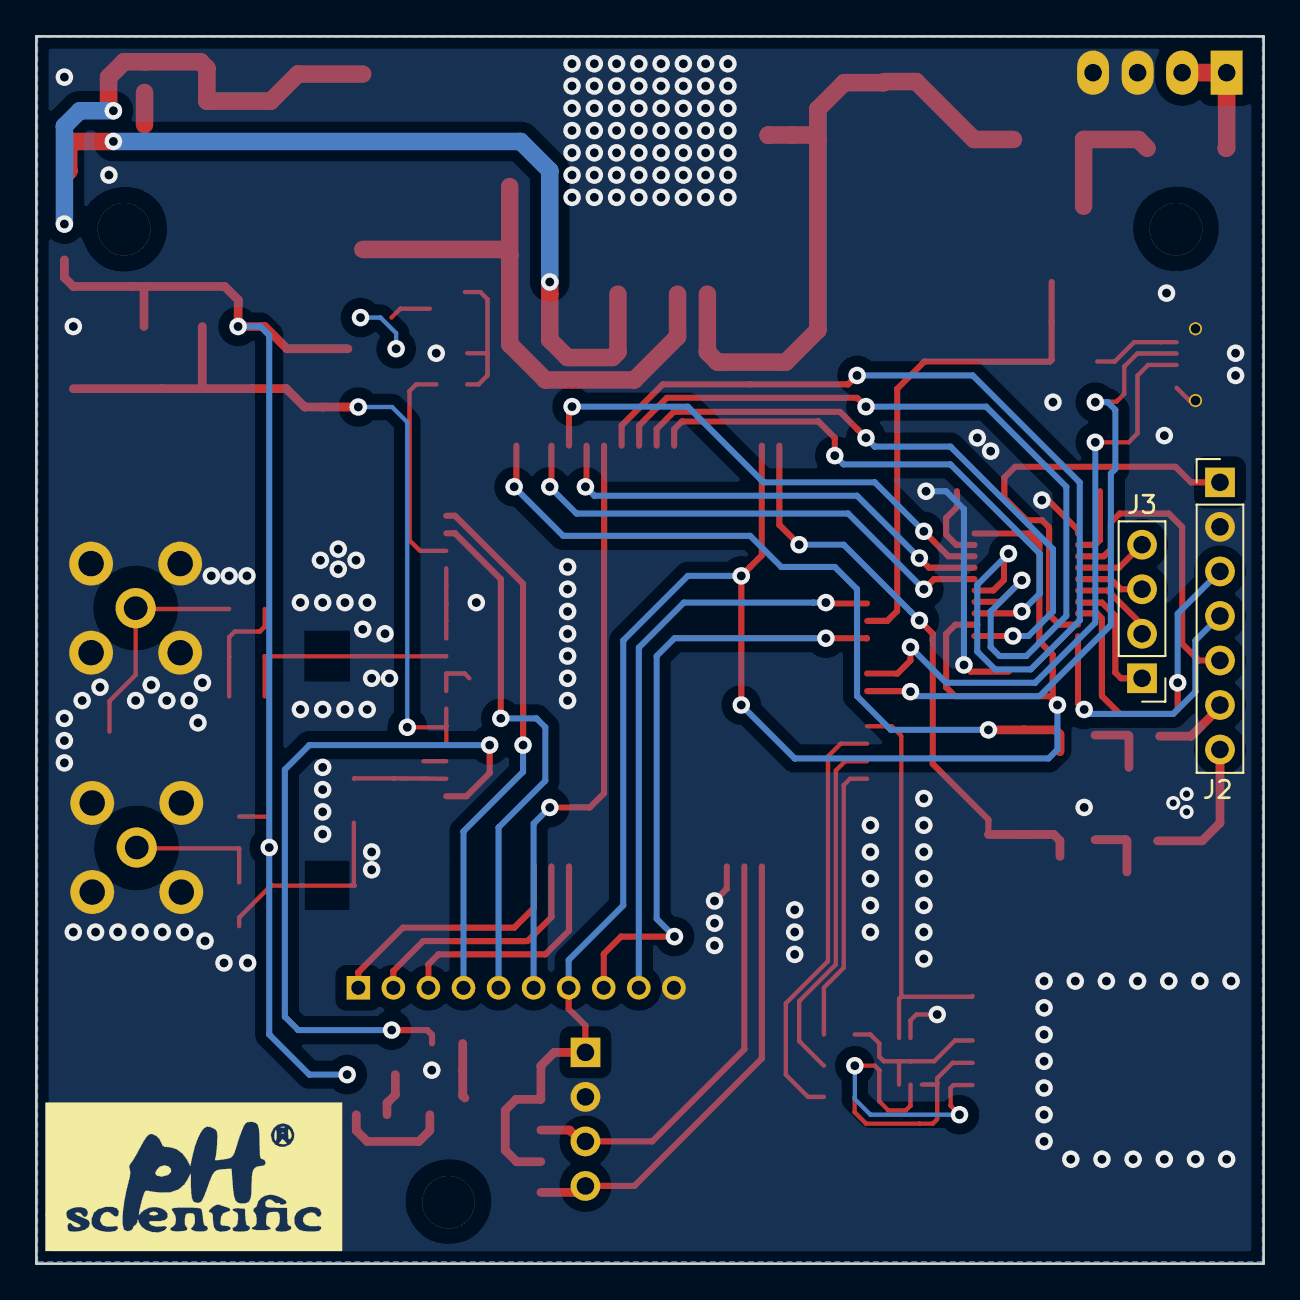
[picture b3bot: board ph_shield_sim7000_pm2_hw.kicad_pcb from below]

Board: 2 copper layers, 70.0 x 70.0 mm, 83 parts (2 on the bottom side), 70 nets.

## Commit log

2019-10-18 Layout_Schematic
2019-10-18 Darwing Layout SIM7000
2019-10-19 Design Schematic SIM7000E
2019-10-20 SIM7000E
2019-10-20 SIM7000E layouting
2019-10-22 Board SIM7000E is finished
2019-10-22 Board Varesistor
2019-10-23 Layout board varesistor is finished
2019-10-23 Darwing board fume hood
2019-10-24 Layoutting board fume_hood
2019-10-25 Layoutting Board Door-Fume-Hood
2019-10-29 door_fume_hood
2019-11-01 Layoutting door fume
2019-11-02 edit mass
2019-11-02 Layout Fume_hood is finished
2019-11-04 Edit power for fume hood
2019-11-05 The door fume hood
2019-11-26 Edited position board analyzer
2019-12-17 Update BOM
2020-01-17 Update file
